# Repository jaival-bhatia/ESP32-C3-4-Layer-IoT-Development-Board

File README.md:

# ESP32-C3-4-Layer-IoT-Development-Board
A custom-designed 4-layer ESP32-C3 IoT development board featuring USB Type-C, Li-ion battery management, environmental sensing, OLED display, and expandable peripheral interfaces.

<div align="center">

**A Custom 4-Layer ESP32-C3 Development Board for Battery-Powered IoT Applications**

</div>

---

# Overview

This project presents a **custom-designed 4-layer ESP32-C3 IoT Development Board** built for low-power, battery-operated embedded applications. The board combines wireless connectivity, intelligent power management, onboard environmental sensing, expandable storage, and a compact PCB layout into a single development platform.

The primary objective of this project was to design a production-ready embedded hardware platform capable of supporting rapid IoT prototyping while following professional PCB design practices such as dedicated power and ground planes, optimized signal routing, proper decoupling, and manufacturing-ready documentation.

Designed entirely in **KiCad**, the board integrates battery charging, USB Type-C connectivity, environmental sensing, local data storage, and display capabilities, making it suitable for a wide range of embedded applications.

---

# Key Features

- 4-Layer PCB designed using KiCad
- ESP32-C3 Wi-Fi + Bluetooth Low Energy (BLE) SoC
- USB Type-C interface for programming and charging
- TP4056 Li-ion battery charging circuit
- Single-cell Li-ion battery support
- Onboard BME280 environmental sensor
- Ambient Light Sensor
- Sound Sensor Interface
- I²C OLED Display Connector
- SPI Flash Memory
- MicroSD Card Storage
- Battery Status LEDs
- Low-Power Embedded Design
- Expandable GPIO Header
- Manufacturing Ready (ERC/DRC Verified)

---

# Hardware Specifications

| Parameter | Description |
|------------|-------------|
| Microcontroller | ESP32-C3 |
| PCB Layers | 4 |
| Power Input | USB Type-C |
| Battery | 3.7V Li-ion |
| Charging IC | TP4056 |
| Connectivity | Wi-Fi + BLE |
| Display | OLED (I²C) |
| Sensors | BME280, Ambient Light, Sound |
| Storage | SPI Flash + microSD |
| Design Software | KiCad |

---

# System Architecture

```
                  USB Type-C
                       │
                       ▼
                TP4056 Charger
                       │
         ┌─────────────┴─────────────┐
         │                           │
         ▼                           ▼
   Li-ion Battery              USB Power
         │                           │
         └─────────────┬─────────────┘
                       ▼
                 3.3V Regulation
                       │
                       ▼
                  ESP32-C3 MCU
      ┌────────┬────────┬────────┬────────┐
      │        │        │        │
      ▼        ▼        ▼        ▼
   OLED     BME280   Flash    microSD
      │
      ▼
 Additional Sensors & GPIO Expansion
```

---

# Power Architecture

The board supports dual power operation through USB Type-C and a rechargeable Li-ion battery.

Power flow:

```
USB Type-C
      │
      ▼
TP4056 Charger
      │
      ▼
Li-ion Battery
      │
      ▼
Voltage Regulation
      │
      ▼
ESP32-C3 + Peripherals
```

The TP4056 charging IC provides:

- Constant Current Charging
- Constant Voltage Charging
- Automatic Charge Termination
- Thermal Protection
- Battery Status Indication

This enables safe battery charging while simultaneously powering the embedded system.

---

# Major Components

| Component | Function |
|-----------|----------|
| ESP32-C3 | Main Microcontroller |
| TP4056 | Li-ion Battery Charger |
| USB Type-C | Power & Programming |
| BME280 | Temperature, Humidity & Pressure |
| OLED Display | Real-time Visualization |
| Flash Memory | Firmware/Data Storage |
| microSD | External Data Logging |

---

# PCB Design Highlights

Highlights include:

- 4-Layer PCB Stack-up
- Dedicated Ground Plane
- Dedicated Power Plane
- Optimized Component Placement
- Short High-Speed Signal Routing
- Proper Decoupling Capacitor Placement
- Optimized Power Distribution
- Low-Noise Analog Routing
- Manufacturing Ready Layout
- ERC & DRC Verified

## Schematics

| Sheet | Description |
|--------|-------------|
| Sheet 1 | USB Type-C & Power Input |
| Sheet 2 | ESP32-C3 Core Circuit |
| Sheet 3 | Sensors & Interfaces |
| Sheet 4 | Battery Charging & Peripheral Connections |

PCB 1st Layer

PCB 2nd Layer

PCB 3rd Layer

PCB 4th Layer

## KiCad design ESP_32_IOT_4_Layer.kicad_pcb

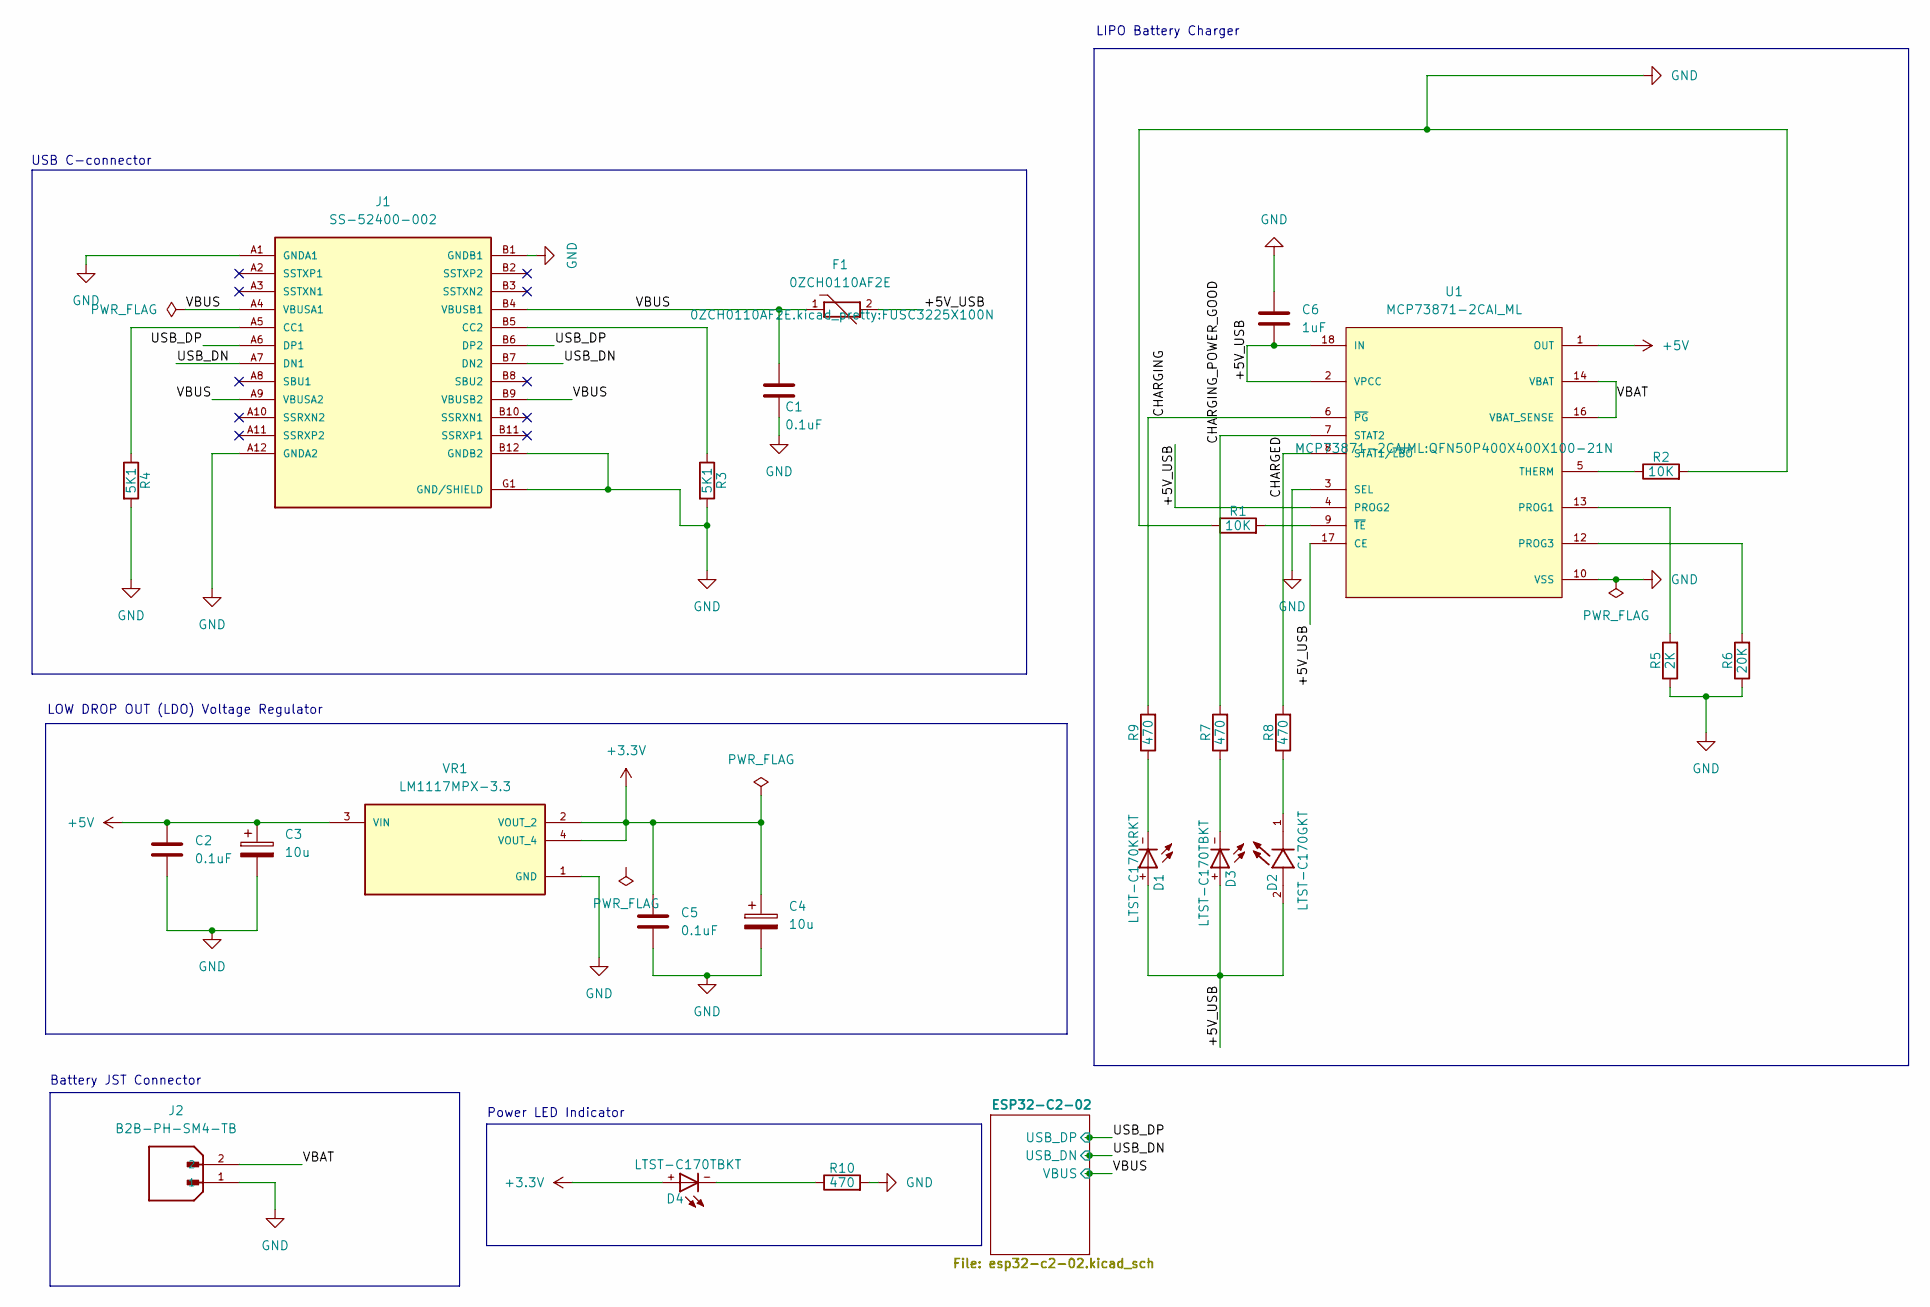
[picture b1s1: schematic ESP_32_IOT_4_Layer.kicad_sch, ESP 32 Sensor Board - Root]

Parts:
C1, C2, C5: 0.1uF; Fuse_0805_2012Metric
C3, C4: 10u; Fuse_0805_2012Metric
C6: 1uF; Fuse_0805_2012Metric
D1: LTST-C170KRKT; DIOC200X125X110; DigiKey_Part_Number 160-1415-1-ND
D2: LTST-C170GKT; LED_LTST-C170GKT; PARTREV I; DigiKey_Part_Number 160-1179-1-ND
D3, D4: LTST-C170TBKT; DIOC200X125X110; DigiKey_Part_Number 160-1579-1-ND
F1: 0ZCH0110AF2E; FUSC3225X100N; PARTREV Apr2023; DigiKey_Part_Number 5923-0ZCH0110AF2ECT-ND
J1: SS-52400-002; BELFUSE_SS-52400-003; PARTREV A0
J2: B2B-PH-SM4-TB; JST_B2B-PH-SM4-TB; PARTREV N/A
R1, R2: 10K; R_0805_2012Metric
R3, R4: 5K1; R_0805_2012Metric
R5: 2K; R_0805_2012Metric
R6: 20K; R_0805_2012Metric
R7, R8, R9, R10: 470; R_0805_2012Metric
U1: MCP73871-2CAI_ML; QFN50P400X400X100-21N; PARTREV D
VR1: LM1117MPX-3.3; VREG_LM1117MPX-3.3; PARTREV O

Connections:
+3.3V: C4.1, C5.1, D4.+, VR1.2 (VOUT_2), VR1.4 (VOUT_4); also elsewhere on the board
+5V: C2.1, C3.1, U1.1 (OUT), U1.20 (OUT), VR1.3 (VIN)
/+5V_USB: C6.2, D1.+, D2.2, D3.+, F1.2, U1.2 (VPCC), U1.4 (PROG2), U1.17 (CE), U1.18 (IN), U1.19 (IN)
/CHARGED: R8.2, U1.8 (STAT1/~LBO)
/CHARGING: R9.2, U1.6 (~PG)
/CHARGING_POWER_GOOD: R7.2, U1.7 (STAT2)
/USB_DN: J1.A7 (DN1), J1.B7 (DN2); also elsewhere on the board
/USB_DP: J1.A6 (DP1), J1.B6 (DP2); also elsewhere on the board
/VBAT: J2.2, U1.14 (VBAT), U1.15 (VBAT), U1.16 (VBAT_SENSE)
/VBUS: C1.1, F1.1, J1.A4 (VBUSA1), J1.A9 (VBUSA2), J1.B4 (VBUSB1), J1.B9 (VBUSB2); also elsewhere on the board
GND: C1.2, C2.2, C3.2, C4.2, C5.2, C6.1, J1.A1 (GNDA1), J1.A12 (GNDA2), J1.B1 (GNDB1), J1.B12 (GNDB2), J1.G1 (GND/SHIELD), J1.G2 (GND/SHIELD), J1.G3 (GND/SHIELD), J1.G4 (GND/SHIELD), J1.S1 (GND/SHIELD), J1.S2 (GND/SHIELD), J1.S3 (GND/SHIELD), J1.S4 (GND/SHIELD), J2.1, R1.1, R2.2, R3.2, R4.2, R5.1, R6.1, R10.2, U1.3 (SEL), U1.10 (VSS), U1.11 (VSS), U1.21 (VSS), VR1.1 (GND); also elsewhere on the board
unnamed: D1.-, R9.1
unnamed: D2.1, R8.1
unnamed: D3.-, R7.1
unnamed: D4.-, R10.1
unnamed: J1.A5 (CC1), R4.1
unnamed: J1.B5 (CC2), R3.1
unnamed: R5.2, U1.13 (PROG1)
unnamed: R6.2, U1.12 (PROG3)
unnamed: R2.1, U1.5 (THERM)
unnamed: R1.2, U1.9 (~TE)

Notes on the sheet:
LOW DROP OUT (LDO) Voltage Regulator
Power LED Indicator
Battery JST Connector
USB C-connector
LIPO Battery Charger

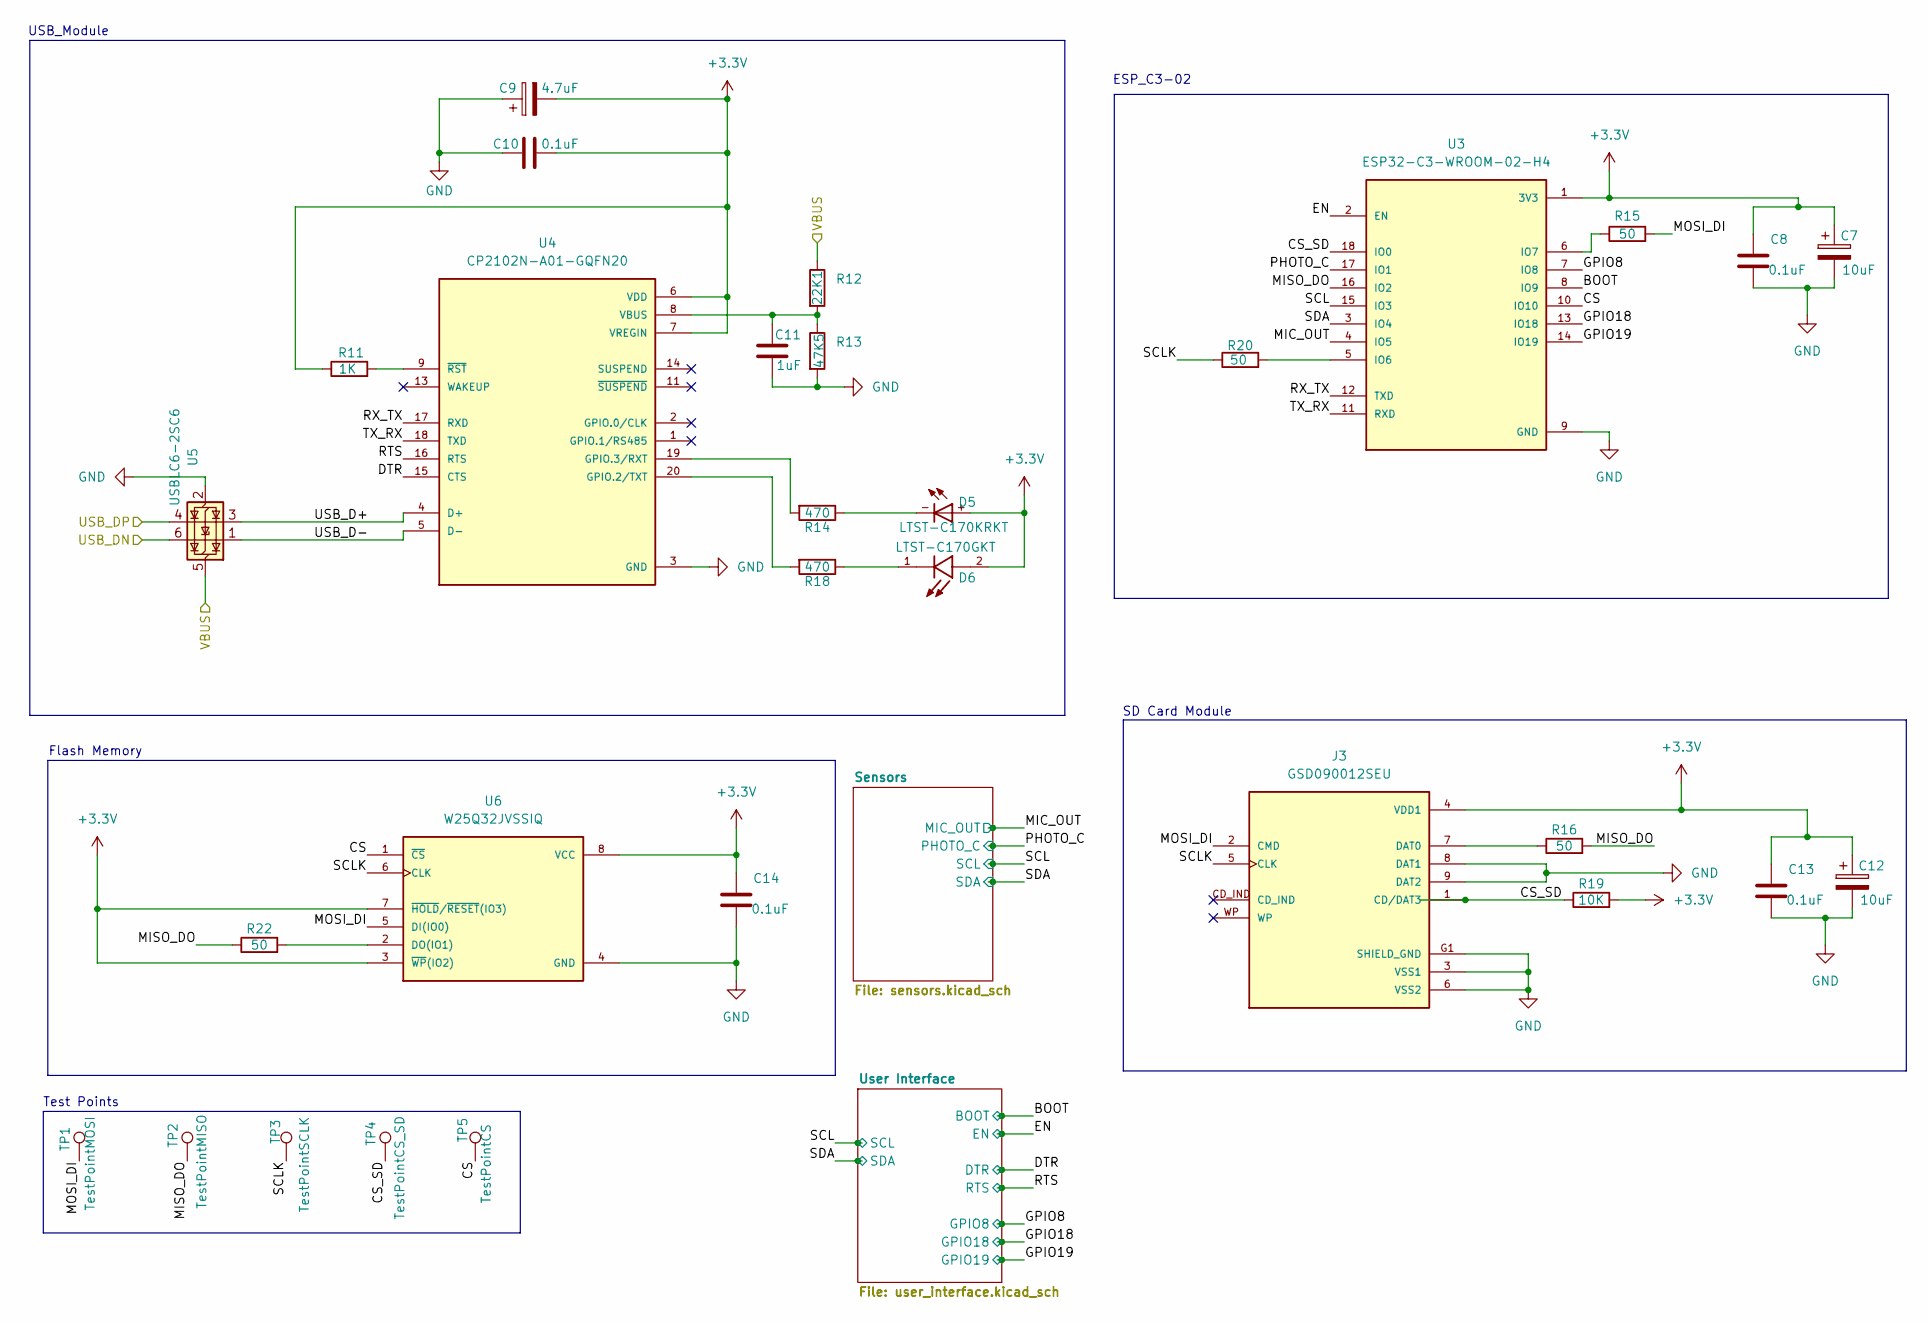
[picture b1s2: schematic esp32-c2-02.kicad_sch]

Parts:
C7, C12: 10uF; Fuse_0805_2012Metric
C8, C10, C13, C14: 0.1uF; Fuse_0805_2012Metric
C9: 4.7uF; Fuse_0805_2012Metric
C11: 1uF; Fuse_0805_2012Metric
D5: LTST-C170KRKT; DIOC200X125X110; DigiKey_Part_Number 160-1415-1-ND
D6: LTST-C170GKT; LED_LTST-C170GKT; PARTREV I; DigiKey_Part_Number 160-1179-1-ND
J3: GSD090012SEU; AMPHENOL_GSD090012SEU; PARTREV E
R11: 1K; R_0805_2012Metric
R12: 22K1; R_0805_2012Metric
R13: 47K5; R_0805_2012Metric
R14, R18: 470; R_0805_2012Metric
R15, R16, R20, R22: 50; R_0805_2012Metric
R19: 10K; R_0805_2012Metric
TP1: TestPointMOSI; TestPoint_Pad_D1.0mm
TP2: TestPointMISO; TestPoint_Pad_D1.0mm
TP3: TestPointSCLK; TestPoint_Pad_D1.0mm
TP4: TestPointCS_SD; TestPoint_Pad_D1.0mm
TP5: TestPointCS; TestPoint_Pad_D1.0mm
U3: ESP32-C3-WROOM-02-H4; MODULE_ESP32-C3-WROOM-02-H4
U4: CP2102N-A01-GQFN20; IC_CP2102N-A01-GQFN20
U5: USBLC6-2SC6; SOT95P280X145-6N
U6: W25Q32JVSSIQ; SOIC127P790X216-8N

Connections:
+3.3V: C7.1, C8.1, C9.2, C10.2, C12.1, C13.1, C14.1, D5.+, D6.2, J3.4 (VDD1), R11.1, R19.2, U3.1 (3V3), U4.6 (VDD), U4.7 (VREGIN), U6.3 (~WP(IO2)), U6.7 (~HOLD/~RESET(IO3)), U6.8 (VCC); also elsewhere on the board
/ESP32-C2-02/BOOT: U3.8 (IO9); also elsewhere on the board
/ESP32-C2-02/CS: TP5.1 (1_1), U3.10 (IO10), U6.1 (~CS)
/ESP32-C2-02/CS_SD: J3.1 (CD/DAT3), R19.1, TP4.1 (1_1), U3.18 (IO0)
/ESP32-C2-02/DTR: U4.15 (CTS); also elsewhere on the board
/ESP32-C2-02/EN: U3.2 (EN); also elsewhere on the board
/ESP32-C2-02/GPIO8: U3.7 (IO8); also elsewhere on the board
/ESP32-C2-02/GPIO18: U3.13 (IO18); also elsewhere on the board
/ESP32-C2-02/GPIO19: U3.14 (IO19); also elsewhere on the board
/ESP32-C2-02/MIC_OUT: U3.4 (IO5); also elsewhere on the board
/ESP32-C2-02/MISO_DO: R16.2, R22.1, TP2.1 (1_1), U3.16 (IO2)
/ESP32-C2-02/MOSI_DI: J3.2 (CMD), R15.2, TP1.1 (1_1), U6.5 (DI(IO0))
/ESP32-C2-02/PHOTO_C: U3.17 (IO1); also elsewhere on the board
/ESP32-C2-02/RTS: U4.16 (RTS); also elsewhere on the board
/ESP32-C2-02/RX_TX: U3.12 (TXD), U4.17 (RXD)
/ESP32-C2-02/SCL: U3.15 (IO3); also elsewhere on the board
/ESP32-C2-02/SCLK: J3.5 (CLK), R20.1, TP3.1 (1_1), U6.6 (CLK)
/ESP32-C2-02/SDA: U3.3 (IO4); also elsewhere on the board
/ESP32-C2-02/TX_RX: U3.11 (RXD), U4.18 (TXD)
/ESP32-C2-02/USB_D+: U4.4 (D+), U5.3 (I/O2)
/ESP32-C2-02/USB_D-: U4.5 (D-), U5.1 (I/O1)
/USB_DN: U5.6 (I/O1); also elsewhere on the board
/USB_DP: U5.4 (I/O2); also elsewhere on the board
/VBUS: R12.1, U5.5 (VBUS); also elsewhere on the board
GND: C7.2, C8.2, C9.1, C10.1, C11.2, C12.2, C13.2, C14.2, J3.3 (VSS1), J3.6 (VSS2), J3.8 (DAT1), J3.9 (DAT2), J3.G1 (SHIELD_GND), J3.G2 (SHIELD_GND), J3.G3 (SHIELD_GND), J3.G4 (SHIELD_GND), R13.2, U3.9 (GND), U3.19 (GND), U3.20 (GND), U3.21 (GND), U3.22 (GND), U3.23 (GND), U3.24 (GND), U3.25 (GND), U3.26 (GND), U3.27 (GND), U3.28 (GND), U3.29 (GND), U3.30 (GND), U3.31 (GND), U3.32 (GND), U3.33 (GND), U3.34 (GND), U3.35 (GND), U3.36 (GND), U3.37 (GND), U3.38 (GND), U3.39 (GND), U4.3 (GND), U4.12 (GND), U4.21 (GND), U5.2 (GND), U6.4 (GND); also elsewhere on the board
unnamed: D5.-, R14.1
unnamed: D6.1, R18.1
unnamed: J3.7 (DAT0), R16.1
unnamed: R20.2, U3.5 (IO6)
unnamed: R15.1, U3.6 (IO7)
unnamed: R18.2, U4.20 (GPIO.2/TXT)
unnamed: R14.2, U4.19 (GPIO.3/RXT)
unnamed: C11.1, R12.2, R13.1, U4.8 (VBUS)
unnamed: R11.2, U4.9 (~RST)
unnamed: R22.2, U6.2 (DO(IO1))

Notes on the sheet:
ESP_C3-02
USB_Module
Test Points
SD Card Module
Flash Memory

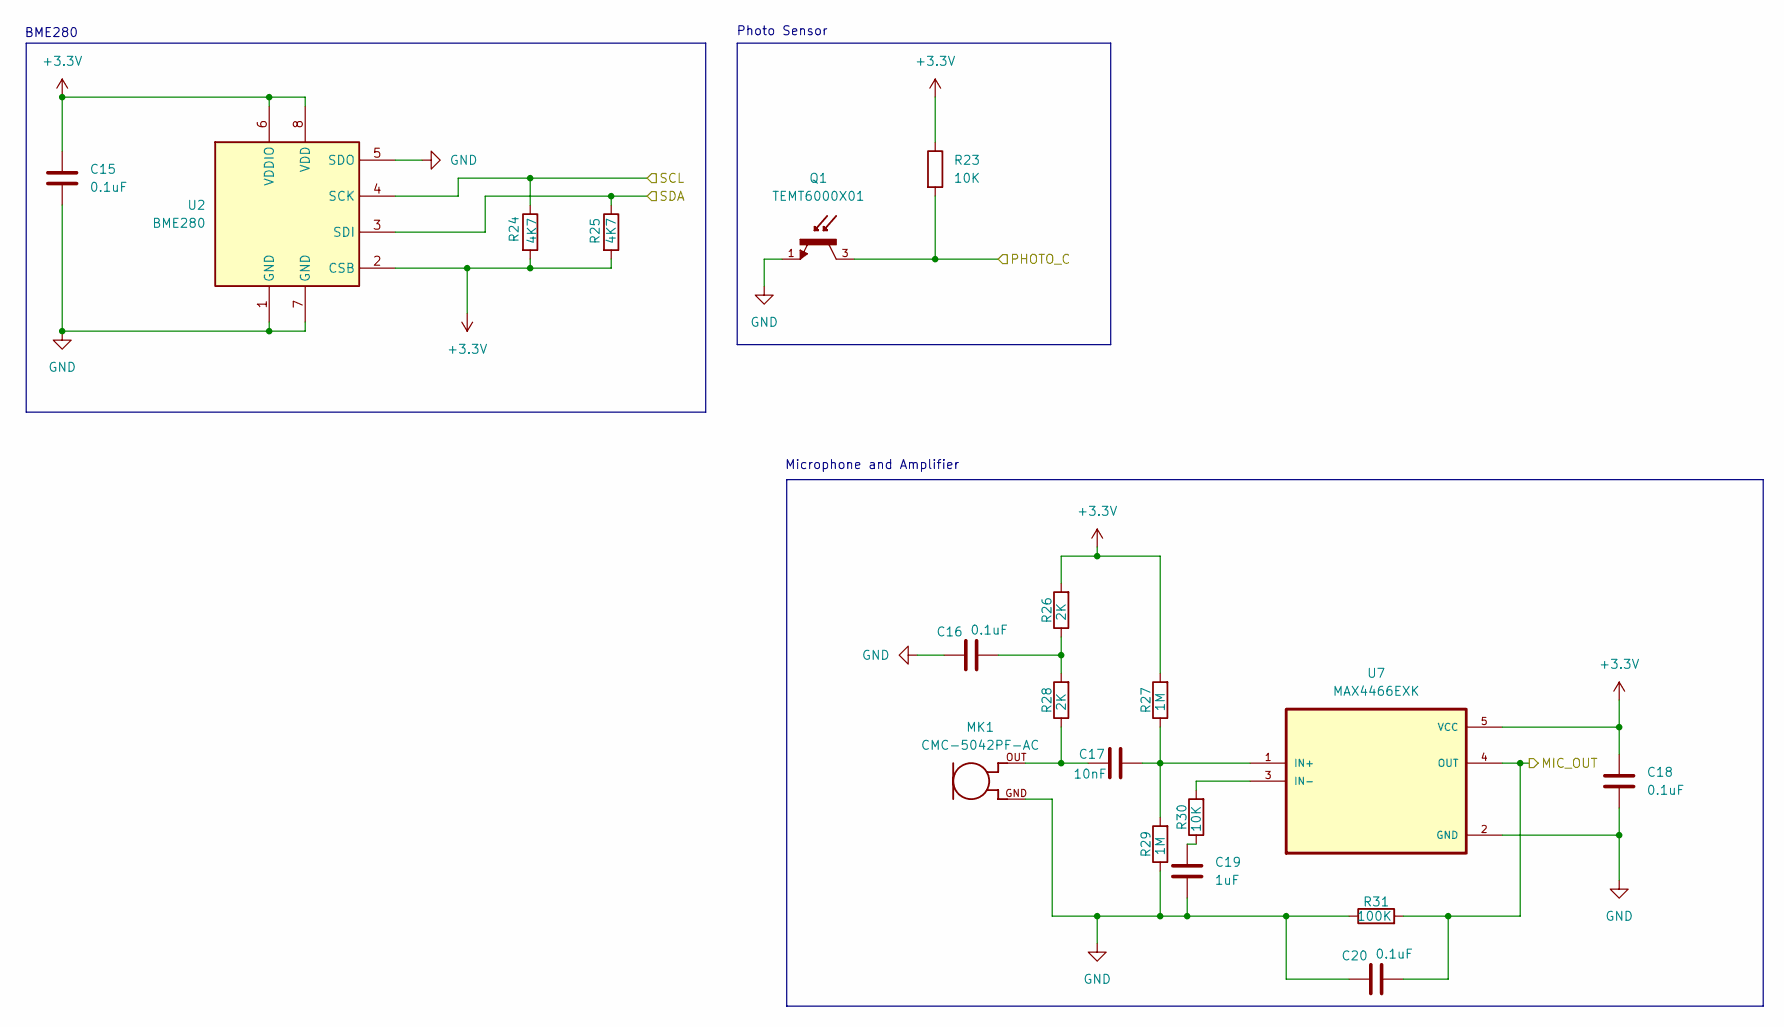
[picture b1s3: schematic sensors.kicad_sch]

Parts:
C15, C16, C18, C20: 0.1uF; Fuse_0805_2012Metric
C17: 10nF; Fuse_0805_2012Metric
C19: 1uF; Fuse_0805_2012Metric
MK1: CMC-5042PF-AC; CUI_CMC-5042PF-AC
Q1: TEMT6000X01; TRANS_TEMT6000X01; PARTREV 1.9
R23, R30: 10K; R_0805_2012Metric
R24, R25: 4K7; R_0805_2012Metric
R26, R28: 2K; R_0805_2012Metric
R27, R29: 1M; R_0805_2012Metric
R31: 100K; R_0805_2012Metric
U2: BME280; PSON65P250X250X100-8N
U7: MAX4466EXK; SOT65P210X110-5N

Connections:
+3.3V: C15.1, C18.1, R23.1, R24.2, R25.2, R26.2, R27.2, U2.2 (CSB), U2.6 (VDDIO), U2.8 (VDD), U7.5 (VCC); also elsewhere on the board
/ESP32-C2-02/MIC_OUT: C20.2, R31.2, U7.4 (OUT); also elsewhere on the board
/ESP32-C2-02/PHOTO_C: Q1.3, R23.2; also elsewhere on the board
/ESP32-C2-02/SCL: R24.1, U2.4 (SCK); also elsewhere on the board
/ESP32-C2-02/SDA: R25.1, U2.3 (SDI); also elsewhere on the board
GND: C15.2, C16.1, C18.2, C19.2, C20.1, MK1.GND, Q1.1, R29.1, R31.1, U2.1 (GND), U2.5 (SDO), U2.7 (GND), U7.2 (GND); also elsewhere on the board
unnamed: C16.2, R26.1, R28.2
unnamed: C17.1, MK1.OUT, R28.1
unnamed: C19.1, R30.1
unnamed: C17.2, R27.1, R29.2, U7.1 (IN+)
unnamed: R30.2, U7.3 (IN-)

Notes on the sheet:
Microphone and Amplifier
Photo Sensor
BME280

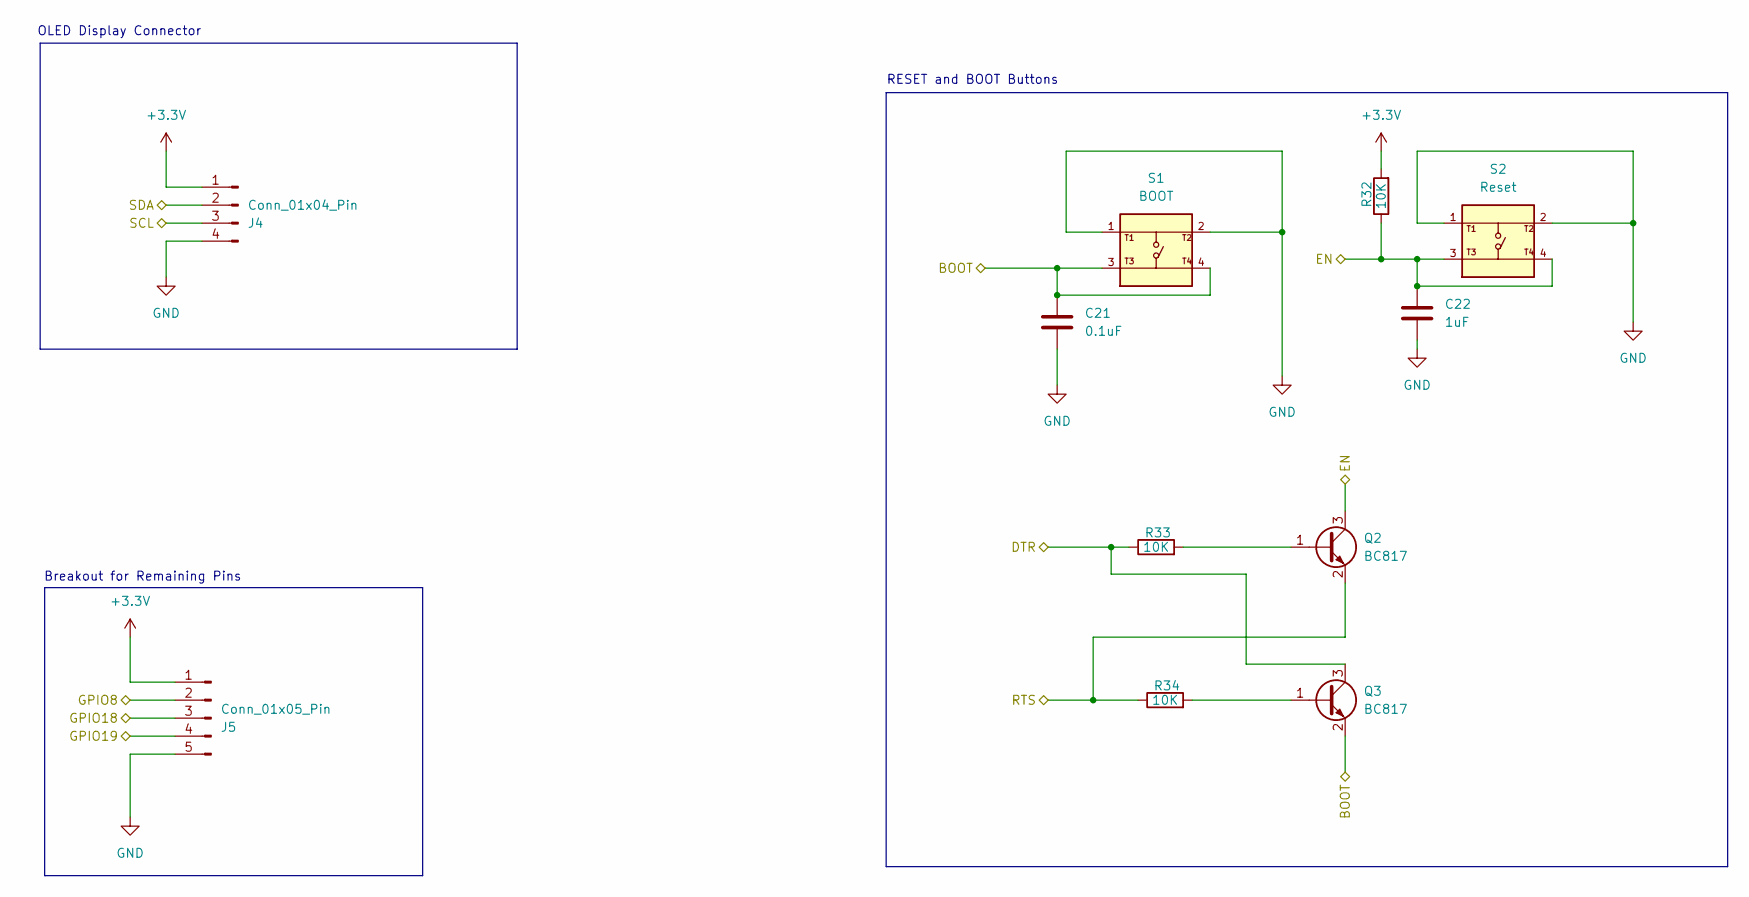
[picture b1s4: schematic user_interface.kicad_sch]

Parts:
C21: 0.1uF; Fuse_0805_2012Metric
C22: 1uF; Fuse_0805_2012Metric
J4: Conn_01x04_Pin; PinHeader_1x04_P2.54mm_Vertical
J5: Conn_01x05_Pin; PinHeader_1x05_P2.54mm_Vertical
Q2, Q3: BC817; SOT-23
R32, R33, R34: 10K; R_0805_2012Metric
S1: BOOT; SW_USLPT2819DT2TR; PARTREV P
S2: Reset; SW_USLPT2819DT2TR; PARTREV P

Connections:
+3.3V: J4.1, J5.1, R32.2; also elsewhere on the board
/ESP32-C2-02/BOOT: C21.1, Q3.2 (E), S1.3, S1.4; also elsewhere on the board
/ESP32-C2-02/DTR: Q3.3 (C), R33.1; also elsewhere on the board
/ESP32-C2-02/EN: C22.1, Q2.3 (C), R32.1, S2.3, S2.4; also elsewhere on the board
/ESP32-C2-02/GPIO8: J5.2; also elsewhere on the board
/ESP32-C2-02/GPIO18: J5.3; also elsewhere on the board
/ESP32-C2-02/GPIO19: J5.4; also elsewhere on the board
/ESP32-C2-02/RTS: Q2.2 (E), R34.1; also elsewhere on the board
/ESP32-C2-02/SCL: J4.3; also elsewhere on the board
/ESP32-C2-02/SDA: J4.2; also elsewhere on the board
GND: C21.2, C22.2, J4.4, J5.5, S1.1, S1.2, S2.1, S2.2; also elsewhere on the board
unnamed: Q2.1 (B), R33.2
unnamed: Q3.1 (B), R34.2

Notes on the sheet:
OLED Display Connector
RESET and BOOT Buttons
Breakout for Remaining Pins

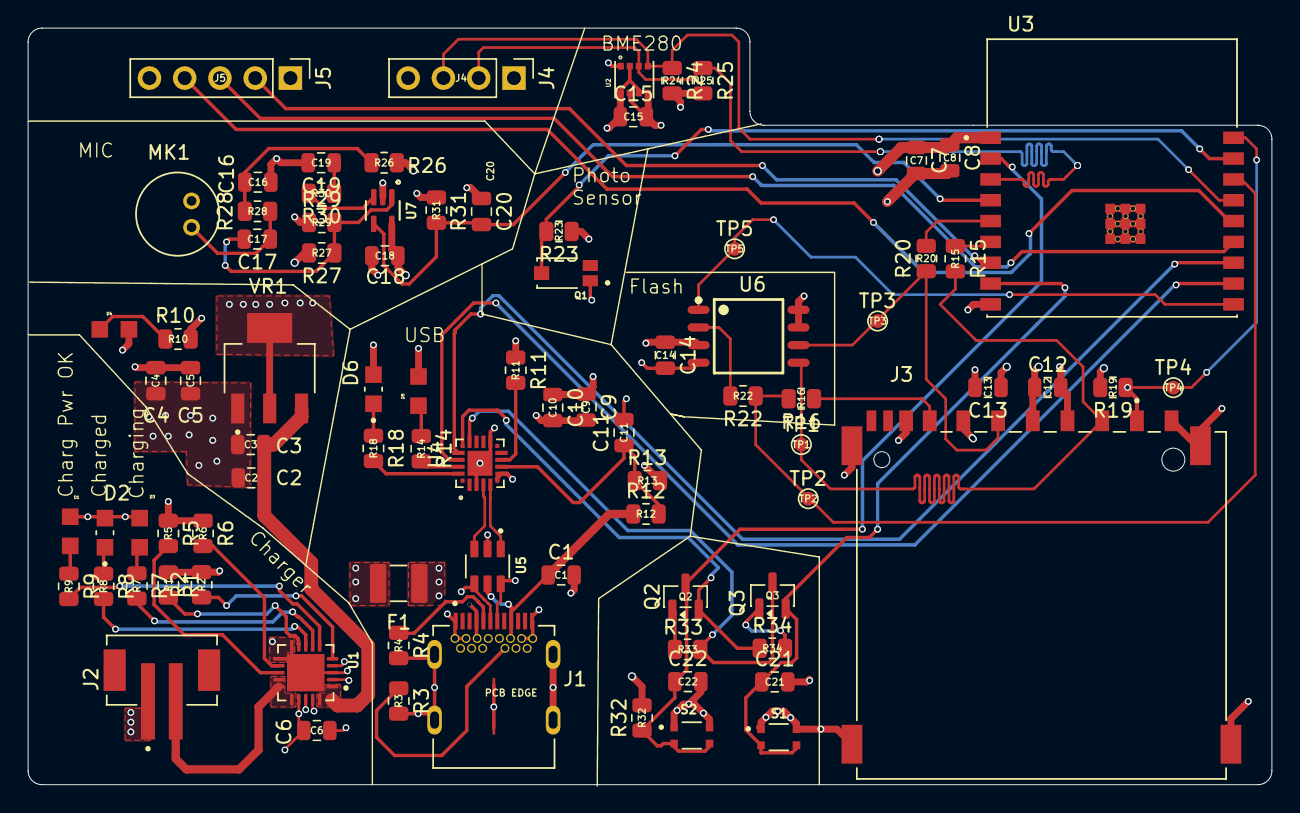
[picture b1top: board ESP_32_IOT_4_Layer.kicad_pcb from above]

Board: 4 copper layers, 89.6 x 54.5 mm, 85 parts (0 on the bottom side), 58 nets.

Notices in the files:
README.md:
MIT License
